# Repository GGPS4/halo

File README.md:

# Halo

An AI cocktail maker that pours by weight. It's a sealed "Gate" design in matte black and
walnut: the glass stands inside an upright ring that lights up as the drink pours, and
eight bottles are hidden in a closed drum behind it. Claude invents drinks from whatever
bottles are loaded.

**Web app:** [try the demo](https://ggps4.github.io/halo/) (sample bottles, simulated pours, runs
in your browser). On your own Halo it's at [http://halo.local:8080](http://halo.local:8080) from
any phone or laptop on the same Wi-Fi. The source is in [`halo/web`](halo/web).

- **Made for a cup of ice.** Set a cup full of ice on the stage and the drink is poured into it,
  ready to drink: no shaking, no stirring beyond a straw. Ingredients go in lightest first
  so the heavy ones (juices, syrups) fall through and mix on the way down, and the
  bartender writes drinks that work built over ice.
- **Sized by alcohol, not volume.** A single holds one standard pour of spirit (1.5 oz of
  40% by default) with the mixers sized around it, so a highball comes out long and a
  spirit-forward drink short, and nothing overflows the cup.
- **Pours by weight, not by timer.** Each pump stops when the scale sees its target grams.
- **Each pump learns.** From the scale, every pump learns how fast it runs and how much
  still lands after it stops, and stops that much early next time. Pours land on target
  with no calibration step, and Halo tells you when a pump has slowed enough that its
  tubing needs replacing.
- **Knows when something's wrong.** Won't pour without a cup, pauses if you lift it, stops
  and tells you which bottle ran dry.
- **Ready until it's picked up.** A finished drink keeps the ring and the gate lit in its
  color until you lift the cup, and Halo won't start the next drink into a cup that's still
  sitting there.
- **Weight guard.** The pump stops if the weight jumps faster than any pump could pour
  (someone pressing on the cup), if the cup gets lighter mid-pour (tipped or spilled), or if
  liquid keeps coming after a pump was switched off (a stuck channel on the board).
- **The light is the progress bar.** The LED ring under the glass, the light strip inside
  the gate (it climbs both sides and meets at the top) and the ring on the round
  touchscreen fill together.
- **Claude bartender.** Tap a mood (sour, strong, low-ABV, surprise me) or type a request
  on your phone. Claude only uses the bottles that are loaded.
- **Strength control.** Light, normal or strong changes how much spirit goes in; the drink
  stays about the same size.
- **Bottle levels.** Every pour is weighed and subtracted from the bottle, so Halo warns you
  before a bottle runs dry and keeps a pour history.
- **Party mode.** Give a theme and Claude writes a short menu from your shelf; the touchscreen
  then shows only those drinks. You can also pick the menu yourself.
- **Pour colors.** The LED ring and the on-screen ring split into each ingredient's share in
  its own color and fill as the drink pours.
- **Soft stop.** Pumps slow down over the last few grams so each ingredient stops on target.
- **Ambient mode.** When idle, the ring and the screen drift through your bottles' colors.
- **Levi voice orders.** `POST /api/voice` with what Levi heard; Halo picks or invents the drink.
- **Drip tray.** A removable tray with a slotted grille surrounds the glass stage.
- **Self-clean from the app.** Settings › Clean Halo walks you through it: a catch cup on
  the stage, all 8 dip tubes in soapy water, then clean water, then air. Halo flushes every
  line, pump and the nozzle, asks you to empty the catch cup before it overflows, flags any
  line that didn't flow, and primes the lines again when the bottles are back.
- **Setup check.** Settings › Run setup check zeroes the scale, checks it against something
  of known weight (and fixes it in one tap), tests the lights, then primes each bottle's
  line and times its pump, with a plain fix for anything that fails.
- **Recipe library.** The Library page finds classic drinks from TheCocktailDB that your
  bottles can make, converts their measures to parts, and lets you add one as it is or have
  Claude rework it to pour over ice.

## The Halo app

Open [http://halo.local:8080](http://halo.local:8080) on your phone or laptop (add it to your home screen for an
app icon). From there you can:

- set what's in each of the 8 slots on a top-down map of the machine, mark bottles refilled,
  and swap slots
- browse, search, favorite, add and edit drinks, with a live preview of the ratio and ABV
- pour any drink at single or double size and light, normal or strong
- ask the bartender for a new drink and save the ones you like
- start and end party menus
- find classics your bottles can make in the Library
- clean Halo and run the setup check
- see stats: most-poured drinks, usage by bottle, recent pours
- change ring brightness, ambient mode, drink sizes, low-bottle warnings and voice orders
- download and import your drink library

The full build (parts, wiring, printing, assembly) is in the Halo build guide. Wiring at a
glance: [`docs/img/wiring.png`](docs/img/wiring.png). What to print, in what filament, and how
the pieces join: [`docs/printing.md`](docs/printing.md). The design spec is in
[`docs/design.md`](docs/design.md) and the driver board in [`pcb/`](pcb/).

## Hardware

Raspberry Pi 5 · Halo Driver Board (in `pcb/`) · 8 × 12 V peristaltic pumps · 1 kg load
cell + HX711 · 24-LED WS2812B ring · 5" round 1080×1080 HDMI touchscreen · 12 V 6 A supply
· 12 V→5 V 5 A USB-C buck converter.

| Function | BCM GPIO |
|---|---|
| Pumps 1–8 | 27, 22, 23, 24, 25, 5, 6, 13 |
| HX711 DT / SCK | 4 / 17 |
| LED ring data (SPI0 MOSI) | 10 |

## Install (Raspberry Pi OS Bookworm, 64-bit)

```bash
git clone https://github.com/GGPS4/halo.git ~/halo
cd ~/halo
./scripts/install.sh          # packages, SPI on, venv, autostart service
nano .env                     # ANTHROPIC_API_KEY=sk-ant-...
sudo systemctl start halo
```

Then open `http://halo.local:8080` on your phone, name the 8 bottles, and run Settings ›
Run setup check: it calibrates the scale and primes every line. (`python -m halo.calibrate
scale` and `prime` still work from the command line.)

## Develop without the hardware

```bash
pip install -r requirements-dev.txt
HALO_MOCK=1 python -m halo --windowed     # UI in a window, fake pumps and scale
HALO_MOCK=1 python -m pytest
```

## Config

Copy `config.example.toml` to `config.toml` to change pins, pour sizes, the Claude model,
or the LED brightness. `bottles.json` and `recipes.json` are written by the app.

## Ordering a drink from another device (Levi)

```bash
# what Levi heard, Halo does the rest
curl -X POST http://halo.local:8080/api/voice \
     -H 'content-type: application/json' \
     -d '{"text": "a strong double margarita"}'
# light the ring while Levi is listening
curl -X POST http://halo.local:8080/api/ring -d '{"mode": "listening"}' -H 'content-type: application/json'
# or order an exact drink
curl -X POST http://halo.local:8080/api/pour \
     -H 'content-type: application/json' \
     -d '{"drink": "Garden Highball", "size": "single"}'
# or let Claude invent one:
     -d '{"request": "something smoky and not too sweet"}'
```

`GET /api/status` returns the pour state and progress.

## Safety

Food-grade silicone tubing only; run Settings › Clean Halo after each session, before
sugar can dry in the lines. Keep the 12 V brick and electronics in the base, away from the drip tray. Drink
responsibly.

## License

MIT — see [LICENSE](LICENSE).

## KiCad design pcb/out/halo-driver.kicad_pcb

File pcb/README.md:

# Halo Driver Board v1.0

A 100 × 70 mm 2-layer board that stacks on a Raspberry Pi 5 like a HAT. The top 65 × 56.5 mm
matches the HAT mounting holes; the rest overhangs past the Pi's SD-card edge and carries the
power input and pump connectors.

## Circuit

| Block | Parts | Notes |
|---|---|---|
| 12 V input | J2 screw terminal, C1 470 µF/25 V | 12 V bus runs along the bottom layer |
| Pump channel ×8 | Q1–Q8 AO3400A, D1–D8 B5819W, R1–R8 100 Ω, R9–R16 10 kΩ | Low-side switch; pull-down keeps pumps off while the Pi boots |
| LED halo | U1 74AHCT1G125, R17 330 Ω, C2 100 nF, C3 10 µF, J12 JST-XH 3P | 3.3 V → 5 V data buffer, fed from SPI0 MOSI (GPIO10) |
| Load cell | J11 1×4 header | Plug an HX711 module here (GND, SCK, DT, VCC = 3.3 V) |

| Channel | 1 | 2 | 3 | 4 | 5 | 6 | 7 | 8 |
|---|---|---|---|---|---|---|---|---|
| GPIO (BCM) | 27 | 22 | 23 | 24 | 25 | 5 | 6 | 13 |
| Header pin | 13 | 15 | 16 | 18 | 22 | 29 | 31 | 33 |

HX711: DT = GPIO4 (pin 7), SCK = GPIO17 (pin 11). LED data = GPIO10 (pin 19).

## Files

- `out/halo-driver-gerbers.zip`: upload to JLCPCB
- `out/halo-driver-BOM.csv`, `out/halo-driver-CPL.csv`: JLCPCB SMT assembly (top side, SMD parts only)
- `out/halo-driver-hand-solder.csv`: through-hole parts you solder yourself
- `out/halo-driver.kicad_pcb`: open in KiCad 8, press **B** to refill zones, then run DRC
- `generate.py`: the source of all of the above (`python pcb/generate.py`)

## Checks done by the generator

- Copper clearance ≥ 0.2 mm between different nets on both layers (JLCPCB minimum is 0.1 mm)
- 3 mm keep-out around each mounting hole, 0.5 mm from the board edge
- Every net connected (the second 5 V and 3.3 V header pins are joined on the Pi itself)

Before ordering, it's worth opening the `.kicad_pcb` in KiCad and running DRC as a second
opinion, and checking part rotations in JLCPCB's assembly preview.

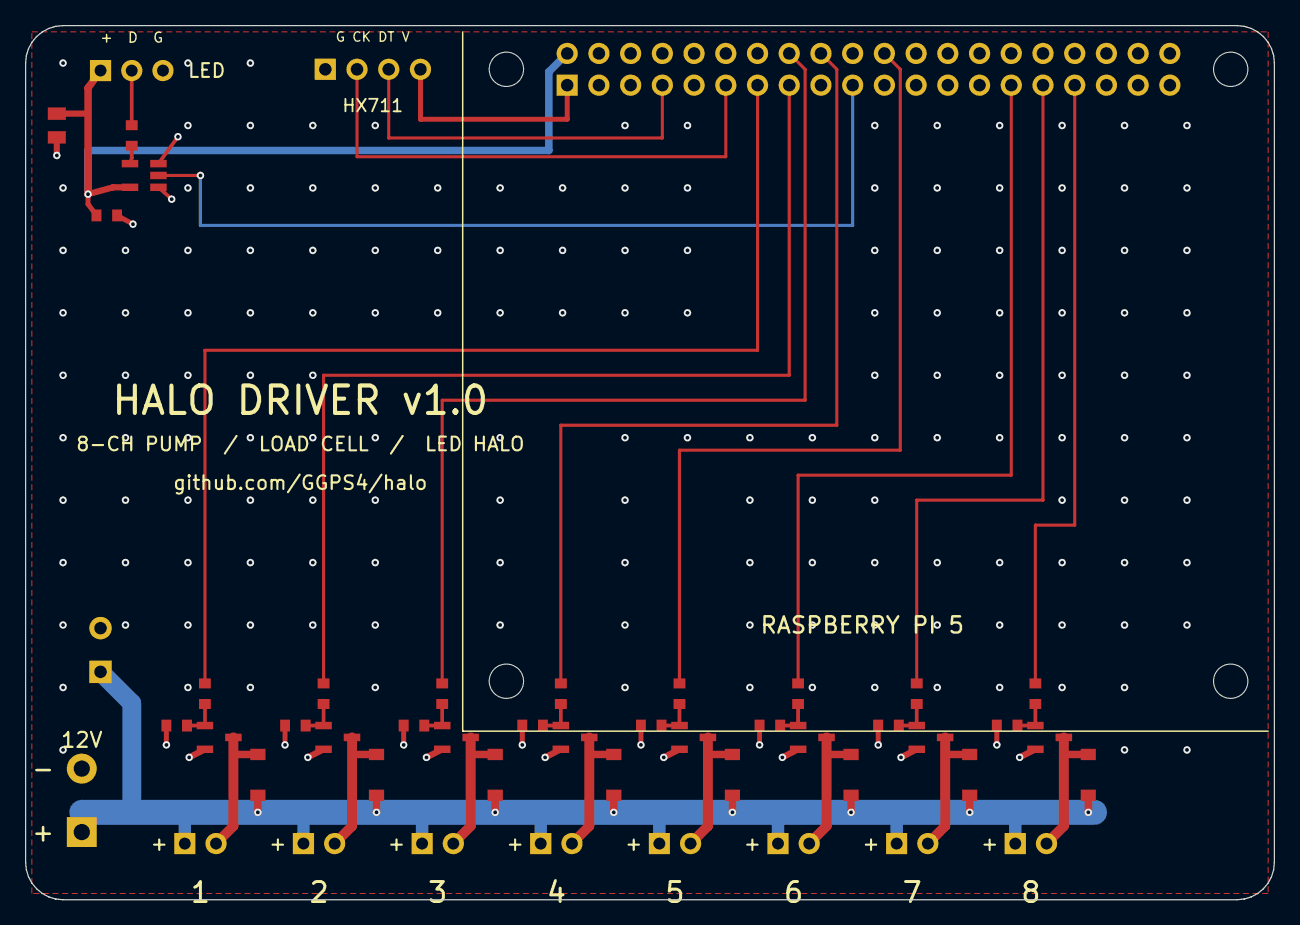
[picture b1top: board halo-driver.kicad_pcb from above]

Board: 2 copper layers, 100.0 x 70.0 mm, 53 parts (0 on the bottom side), 33 nets.

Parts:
C1: 470uF 25V; CP_Radial_D8.0mm_P3.50mm
C2: 100nF; C_0603
C3: 10uF 25V; C_0805
D1, D2, D3, D4, D5, D6, D7, D8: B5819W; D_SOD-123
H1, H2, H3, H4: MountingHole_2.7mm
J1: 2x20 female header; PinSocket_2x20_P2.54
J2: 12V IN KF301-2P; TerminalBlock_5.08_1x02
J3: PUMP 1 JST-XH; JST_XH_B2B-XH-A
J4: PUMP 2 JST-XH; JST_XH_B2B-XH-A
J5: PUMP 3 JST-XH; JST_XH_B2B-XH-A
J6: PUMP 4 JST-XH; JST_XH_B2B-XH-A
J7: PUMP 5 JST-XH; JST_XH_B2B-XH-A
J8: PUMP 6 JST-XH; JST_XH_B2B-XH-A
J9: PUMP 7 JST-XH; JST_XH_B2B-XH-A
J10: PUMP 8 JST-XH; JST_XH_B2B-XH-A
J11: HX711 1x4; PinHeader_1x04_P2.54
J12: LED RING JST-XH 3P; JST_XH_B3B-XH-A
Q1, Q2, Q3, Q4, Q5, Q6, Q7, Q8: AO3400A; SOT-23
R1, R2, R3, R4, R5, R6, R7, R8: 100; R_0603
R9, R10, R11, R12, R13, R14, R15, R16: 10k; R_0603
R17: 330; R_0603
U1: 74AHCT1G125; SOT-23-5

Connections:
+3V3: J1.1, J11.4
+5V: C2.1, C3.1, J1.2, J12.1, U1.5
+12V: C1.1, D1.1, D2.1, D3.1, D4.1, D5.1, D6.1, D7.1, D8.1, J2.1, J3.1, J4.1, J5.1, J6.1, J7.1, J8.1, J9.1, J10.1
GATE1: Q1.1, R1.2, R9.2
GATE2: Q2.1, R2.2, R10.2
GATE3: Q3.1, R3.2, R11.2
GATE4: Q4.1, R4.2, R12.2
GATE5: Q5.1, R5.2, R13.2
GATE6: Q6.1, R6.2, R14.2
GATE7: Q7.1, R7.2, R15.2
GATE8: Q8.1, R8.2, R16.2
GND: C1.2, C2.2, C3.2, J1.6, J1.9, J1.14, J1.20, J1.25, J1.30, J1.34, J1.39, J2.2, J11.1, J12.3, Q1.2, Q2.2, Q3.2, Q4.2, Q5.2, Q6.2, Q7.2, Q8.2, R9.1, R10.1, R11.1, R12.1, R13.1, R14.1, R15.1, R16.1, U1.1, U1.3
GPIO_P1: J1.13, R1.1
GPIO_P2: J1.15, R2.1
GPIO_P3: J1.16, R3.1
GPIO_P4: J1.18, R4.1
GPIO_P5: J1.22, R5.1
GPIO_P6: J1.29, R6.1
GPIO_P7: J1.31, R7.1
GPIO_P8: J1.33, R8.1
HX_DT: J1.7, J11.3
HX_SCK: J1.11, J11.2
LED_DIN: J1.19, U1.2
LED_DOUT: J12.2, R17.1
LED_Y: R17.2, U1.4
PUMP1-: D1.2, J3.2, Q1.3
PUMP2-: D2.2, J4.2, Q2.3
PUMP3-: D3.2, J5.2, Q3.3
PUMP4-: D4.2, J6.2, Q4.3
PUMP5-: D5.2, J7.2, Q5.3
PUMP6-: D6.2, J8.2, Q6.3
PUMP7-: D7.2, J9.2, Q7.3
PUMP8-: D8.2, J10.2, Q8.3

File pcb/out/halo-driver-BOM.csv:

Comment,Designator,Footprint,LCSC Part #
AO3400A,"Q1,Q2,Q3,Q4,Q5,Q6,Q7,Q8",SOT-23,C20917
B5819W,"D1,D2,D3,D4,D5,D6,D7,D8",D_SOD-123,C8598
100,"R1,R2,R3,R4,R5,R6,R7,R8",R_0603,C22775
10k,"R9,R10,R11,R12,R13,R14,R15,R16",R_0603,C25804
74AHCT1G125,U1,SOT-23-5,C7484
330,R17,R_0603,C23138
10uF 25V,C3,C_0805,C15850
100nF,C2,C_0603,C14663
